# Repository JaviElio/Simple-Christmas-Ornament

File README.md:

# Simple-Christmas-Ornament
Christmas Ornament

Based on this project:

	- Title:	ESP8266 Christmas Ornaments!
	- Author:	Sean Hodgins
	- Link:		https://www.instructables.com/id/ESP8266-Christmas-Ornaments/

**BOM:**

(1) Attiny85

(3) WS2812

(1) DC/DC Step up converter ME2108

(1) Buzzer MLT-8530

(1) BC817

(1) SI2302

(1) Push Button

(1) [SMD AAA Batery Holder](https://www.aliexpress.com/item/5Pcs-lot-1-AAA-Battery-Holder-SMD-SMT-High-Quality-Battery-Box-With-Bronze-Pins-TBH/32795495670.html?ws_ab_test=searchweb0_0,searchweb201602_5_10065_10068_10547_319_10891_317_10548_10696_10084_453_454_10083_10618_10307_10820_10821_10301_10303_537_536_10059_10884_10887_321_322_10103,searchweb201603_51,ppcSwitch_0&algo_expid=1f16c75a-10c3-4c96-85c8-67561e371a74-2&algo_pvid=1f16c75a-10c3-4c96-85c8-67561e371a74&transAbTest=ae803_3)

(1) Schottky Diode

(1) M7 Diode

(1) 47uF Capacitor

(1) 0.1uF Capacitor 

(1) 470 Ohm Resistor

(1) 10 kOhm Resistor

**SCHEMATIC:**

 [Schematic PDF](https://github.com/JaviElio/Simple-Christmas-Ornament/blob/master/Schematic.pdf)

**FEATURES:**

This Ornaments plays a song every time the button is pressed. Leds changes its color to the rhythm of the song.
Attiny85 goes to deep sleep to save energy.

**PICTURES**

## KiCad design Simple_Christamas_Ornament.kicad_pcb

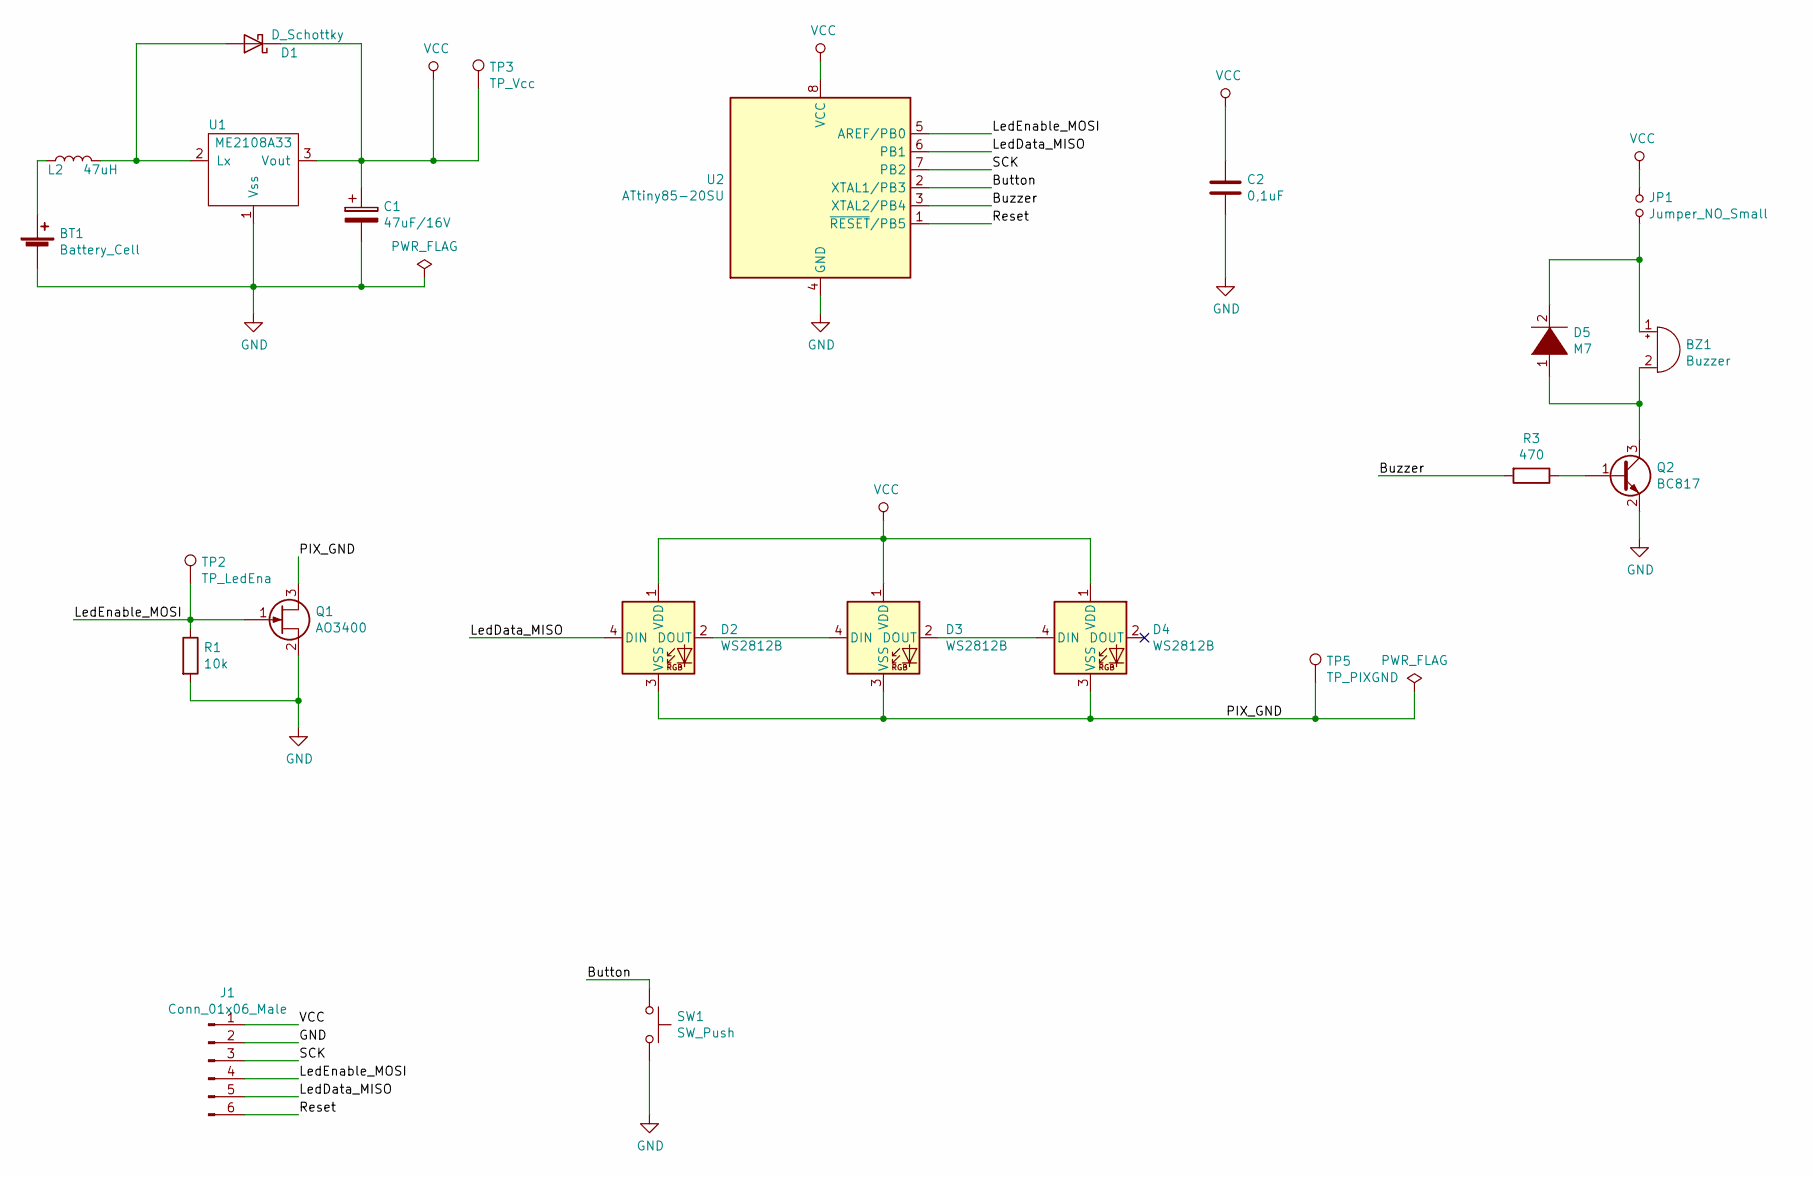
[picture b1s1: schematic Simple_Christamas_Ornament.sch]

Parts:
BT1: Battery_Cell; AAA_SMD_Holder
BZ1: Buzzer; Buzzer_8.5x8.5mm
C1: 47uF/16V; CP_EIA-6032-28_Kemet-C_Pad2.25x2.35mm_HandSolder
C2: 0,1uF; C_0805_2012Metric_Pad1.15x1.40mm_HandSolder
D1: D_Schottky; R_0805_2012Metric_Pad1.15x1.40mm_HandSolder
D2, D3, D4: WS2812B; LED_WS2812B_PLCC4_5.0x5.0mm_P3.2mm
D5: M7; D_SMA_Handsoldering
J1: Conn_01x06_Male; PinHeader_2x03_P2.54mm_Vertical_SMD
JP1: Jumper_NO_Small; R_0805_2012Metric_Pad1.15x1.40mm_HandSolder
L2: 47uH; Inductor_SM5845
Q1: AO3400; SOT-23_Handsoldering
Q2: BC817; SOT-23_Handsoldering
R1: 10k; R_0805_2012Metric_Pad1.15x1.40mm_HandSolder
R3: 470; R_0805_2012Metric_Pad1.15x1.40mm_HandSolder
SW1: SW_Push; SW_PUSH_6mm_H4.3mm
TP2: TP_LedEna; TestPoint_Pad_1.0x1.0mm
TP3: TP_Vcc; TestPoint_Pad_1.0x1.0mm
TP5: TP_PIXGND; TestPoint_Pad_1.0x1.0mm
U1: ME2108A33; SOT-23_Handsoldering
U2: ATtiny85-20SU; SOIJ-8_5.3x5.3mm_P1.27mm

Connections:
/Button: SW1.1, U2.2 (XTAL1/PB3)
/Buzzer: R3.2, U2.3 (XTAL2/PB4)
/LedData_MISO: D2.4 (DIN), J1.5, U2.6 (PB1)
/LedEnable_MOSI: J1.4, Q1.1 (G), R1.1, TP2.1, U2.5 (AREF/PB0)
/PIX_GND: D2.3 (VSS), D3.3 (VSS), D4.3 (VSS), Q1.3 (D), TP5.1
/Reset: J1.6, U2.1 (~RESET~/PB5)
/SCK: J1.3, U2.7 (PB2)
GND: BT1.2 (-), C1.2, C2.2, J1.2, Q1.2 (S), Q2.2 (E), R1.2, SW1.2, U1.1 (Vss), U2.4 (GND)
unnamed: BT1.1 (+), L2.1
unnamed: BZ1.1 (-), D5.2 (A), JP1.1
unnamed: BZ1.2 (+), D5.1 (K), Q2.3 (C)
unnamed: D1.2 (A), L2.2, U1.2 (Lx)
unnamed: D2.2 (DOUT), D3.4 (DIN)
unnamed: D3.2 (DOUT), D4.4 (DIN)
unnamed: Q2.1 (B), R3.1
VCC: C1.1, C2.1, D1.1 (K), D2.1 (VDD), D3.1 (VDD), D4.1 (VDD), J1.1, JP1.2, TP3.1, U1.3 (Vout), U2.8 (VCC)

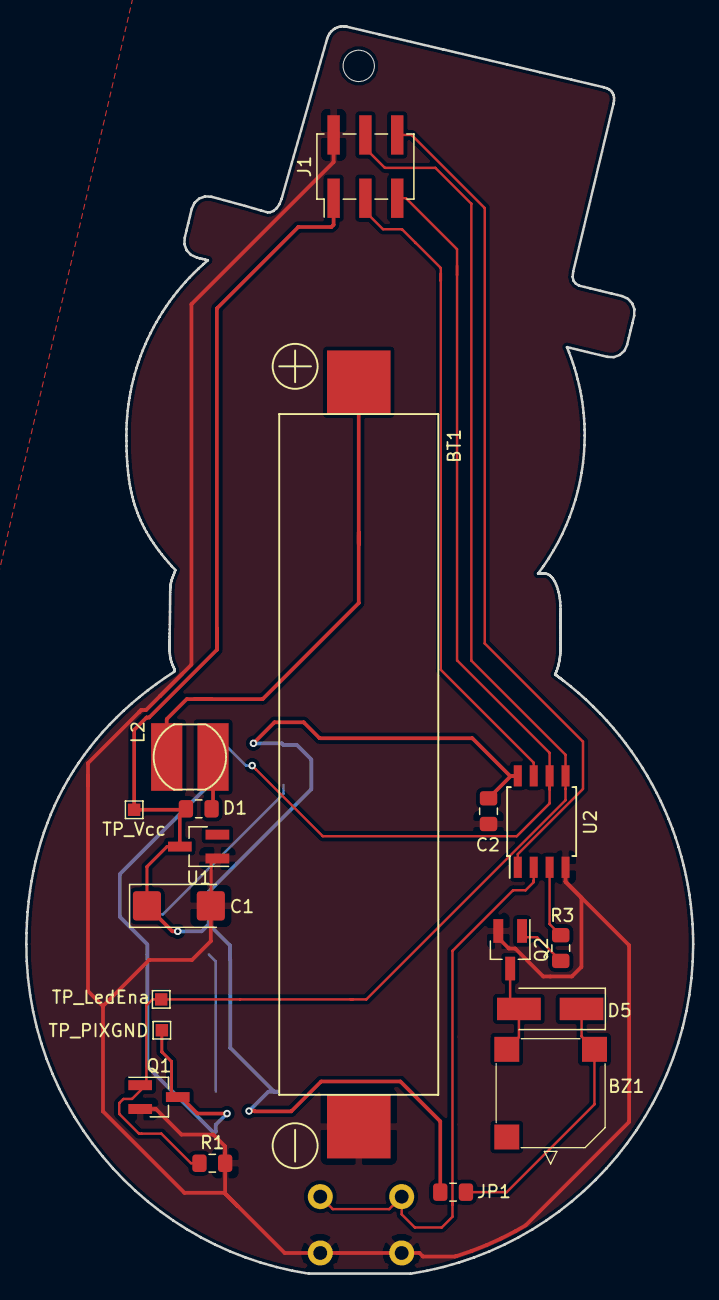
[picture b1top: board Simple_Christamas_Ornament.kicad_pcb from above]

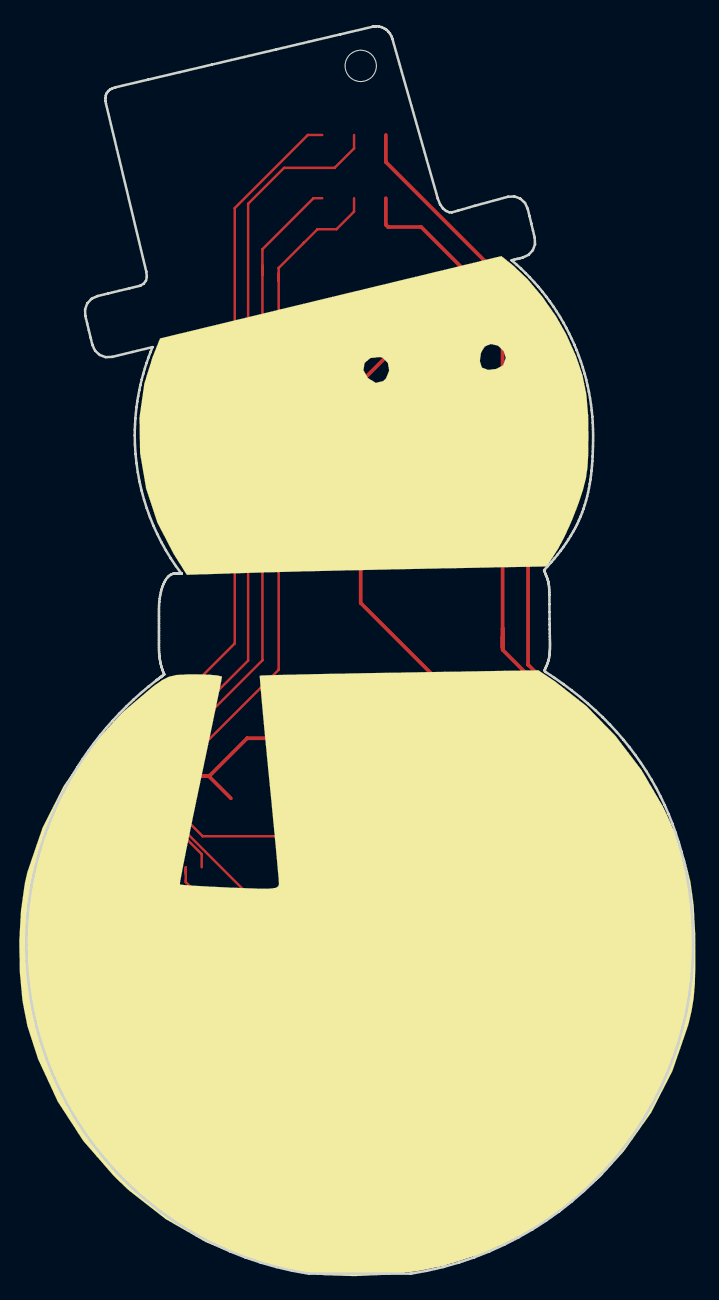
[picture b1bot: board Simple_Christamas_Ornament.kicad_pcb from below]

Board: 2 copper layers, 53.2 x 99.6 mm, 22 parts (4 on the bottom side), 16 nets.

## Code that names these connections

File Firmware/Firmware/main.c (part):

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	if (xbit == 0){
	
		//cli();
		PORTB |= (1 << PB1);
		DELAYCYCLES(NS_TO_CYCLES(TOH)-2);
		PORTB &= ~(1 << PB1);
		//sei();
		DELAYCYCLES(NS_TO_CYCLES(TOL)-1);
		
	}
	else {
		
		PORTB |= (1 << PB1);
		DELAYCYCLES(NS_TO_CYCLES(T1H)-2);
		PORTB &= ~(1 << PB1);
		DELAYCYCLES(NS_TO_CYCLES(T1L)-1);
		
	}
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		if (xByte & (0x01 << i))
		{
			
			PORTB |= (1 << PB1);
			DELAYCYCLES(NS_TO_CYCLES(T1H)-2);
			PORTB &= ~(1 << PB1);
			DELAYCYCLES(NS_TO_CYCLES(T1L)-4);

		}
		else
		{
			//cli();
			PORTB |= (1 << PB1);
			DELAYCYCLES(NS_TO_CYCLES(TOH)-2);
			PORTB &= ~(1 << PB1);
			//sei();
			DELAYCYCLES(NS_TO_CYCLES(TOL)-4);
		}
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
void switchOffLeds() {

	PORTB &= ~(1 << PB1);	// OUTPUT -> 0
	DDRB  &= ~(1 << PB1);   // PB1->INPUT (Hi-Z)
	PORTB &= ~(1 << PB0);	// Switch off MOSFET
}

void switchOnLeds() {
	
	PORTB |= (1 << PB0);	// Switch on MOSFET
	_delay_ms(1);
	DDRB  |= (1 << PB1);    // PB1 -> OUTPUT
	PORTB &= ~(1 << PB1);	// OUTPUT -> 0
}


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	
	switchOnLeds();
	
	GTCCR |= (1 << COM1B0);																		// Connect timer to PB4 and toggle on CTC
	
	for (uint8_t i=0; i<Mariolength; i++) {

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		_delay_ms(35);																			// Pause between notes.
	}
	
	GTCCR &= ~( 1 << COM1B0);																	// Disconnect from PB4
	PORTB &= ~( 1 << PB4);																		// Switch off PB4
	
	switchOffLeds();
}
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	
	switchOnLeds();
	
	GTCCR |= (1 << COM1B0);																	// Connect timer to PB4 and toggle on CTC
		
	for (uint8_t i=0; i<songLenght; i++) {
		
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		_delay_ms(50);																		// Pause between notes
	}
		
	GTCCR &= ~( 1 << COM1B0);																// Disconnect from PB4
	PORTB &= ~( 1 << PB4);																	// Switch off PB4
	
	switchOffLeds();
	
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{
	
	// Setup I/O
	DDRB |= (1 << PB1);					// Neopixel Data Output
	DDRB |= (1 << PB0);					// Neopixel enable
	DDRB |= (1 << PB4);					// Buzzer output
	DDRB &= ~(1 << PB3);				// Button input
	PORTB |= (1 << PB3);				// Pull-up resistor


	switchOffLeds();
			
	// Setup interrupt on PB3
	PCMSK |= ( 1 << PCINT3);		// Enable Pin Change Interrupt on PB3
	GIMSK |= ( 1 << PCIE);			// Enable Pin Change Interrupts
	sei();
	
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
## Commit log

2019-04-03 First Upload
2019-04-03 Pictures uploaded
2019-04-03 Readme updated
2019-04-03 Schematic and excel file uploaded
